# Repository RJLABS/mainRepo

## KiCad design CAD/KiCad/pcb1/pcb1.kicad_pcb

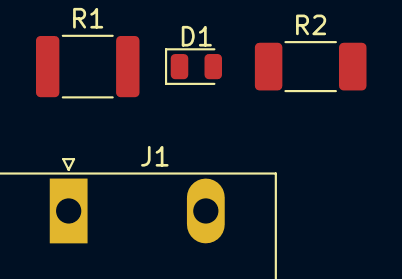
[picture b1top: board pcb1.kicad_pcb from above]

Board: 2 copper layers, 4 parts (0 on the bottom side), 3 nets, no tracks yet.

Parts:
D1: LED_Dual_ACA; LED_0805_2012Metric
J1: Conn_01x04_Female; PhoenixContact_GMSTBA_2,5_2-G-7,62_1x02_P7.62mm_Horizontal
R1: R_US; R_1812_4532Metric_Pad1.30x3.40mm_HandSolder
R2: R_US; R_2010_5025Metric_Pad1.52x2.65mm_HandSolder

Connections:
unnamed: D1.1, R1.2
unnamed: D1.2, J1.2, R2.1
unnamed: J1.1, R1.1

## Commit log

2018-08-22 smartRelay v.1
    uno
2018-08-23 tes avrcode
2018-08-23 ADD PLC FOLDER
2018-08-24 add tutorial
    universitas negri malang
2018-08-24 tes rung plc
2018-08-29 add scurity motocycle projek
2018-08-31 MQTT projek
2018-08-31 PLUG IN ARDUINO SUBLIME
2018-08-31 MOVE FOLDER
2018-08-31 RESTORE DELETED ITEM
2018-09-03 MQTT FILE
2018-09-13 CAD FOLDER
2018-09-24 BLDC FIRMWARE
2018-10-05 MQTT ESP8266
2018-10-05 PLC FILE
2018-10-15 esp mqtt lcd i2c
2018-10-30 maximize
2018-11-13 delet cad
2018-11-13 delet unused file
2018-11-13 delet usles projek
